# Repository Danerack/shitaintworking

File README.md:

4dawg Im about to tweak out rn

why is Hackatime and summer not workingggg
4rncrf htn unjth j

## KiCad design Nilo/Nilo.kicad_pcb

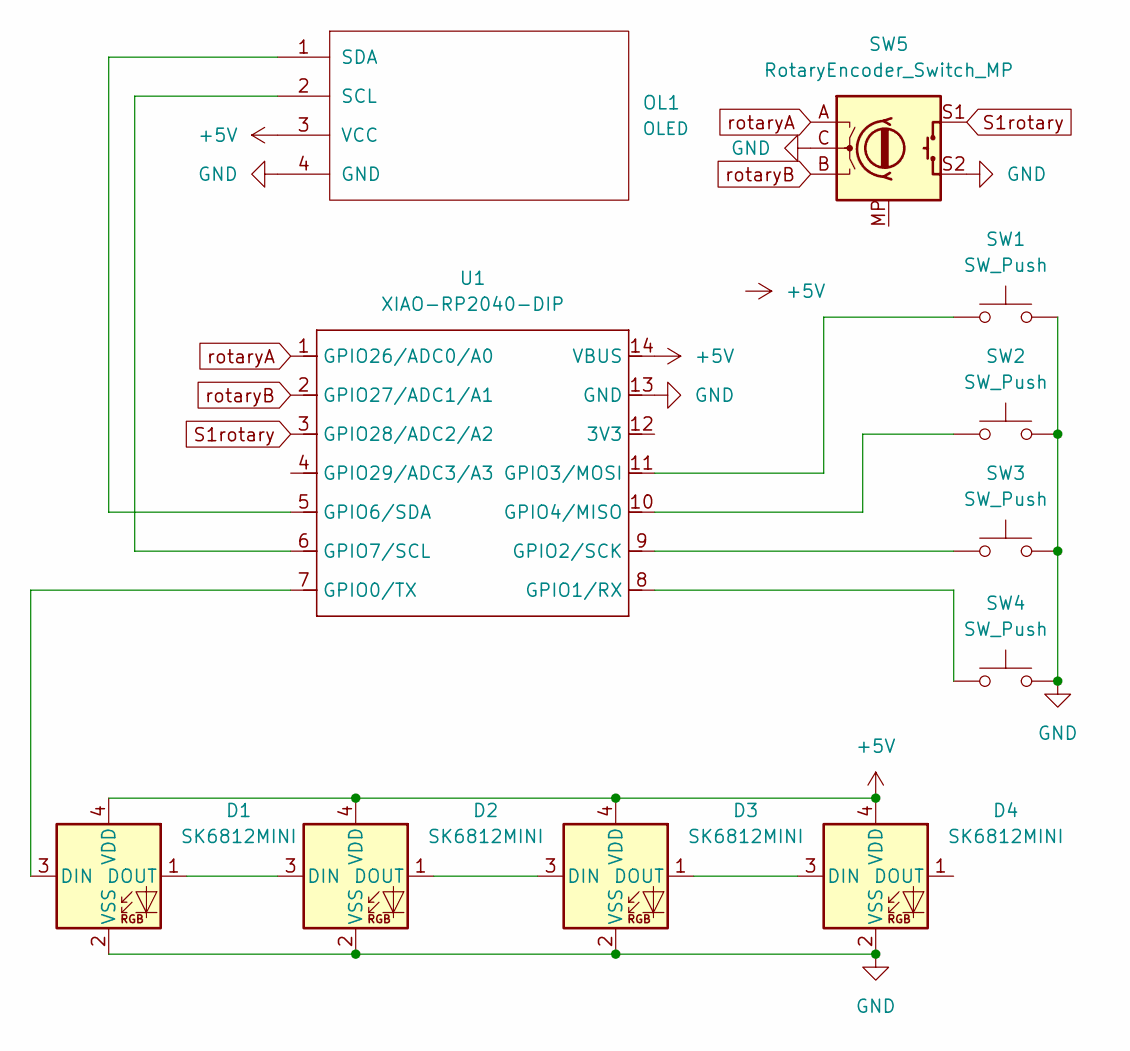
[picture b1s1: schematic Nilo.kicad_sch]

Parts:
D1, D2, D3, D4: SK6812MINI; LED_SK6812MINI_PLCC4_3.5x3.5mm_P1.75mm_3D
OL1: OLED
SW1, SW2, SW3, SW4: SW_Push; SW_Cherry_MX_1.00u_PCB_3D
SW5: RotaryEncoder_Switch_MP; RotaryEncoder_Alps_EC11E-Switch_Vertical_H20mm_3D
U1: XIAO-RP2040-DIP; XIAO-RP2040-DIP_3D

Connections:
+5V: D1.4 (VDD), D2.4 (VDD), D3.4 (VDD), D4.4 (VDD), OL1.3 (VCC), U1.14 (VBUS)
GND: D1.2 (VSS), D2.2 (VSS), D3.2 (VSS), D4.2 (VSS), OL1.4 (GND), SW1.2, SW2.2, SW3.2, SW4.2, SW5.C, SW5.S2, U1.13 (GND)
unnamed: D1.3 (DIN), U1.7 (GPIO0/TX)
unnamed: D1.1 (DOUT), D2.3 (DIN)
unnamed: D2.1 (DOUT), D3.3 (DIN)
unnamed: D3.1 (DOUT), D4.3 (DIN)
unnamed: OL1.2 (SCL), U1.6 (GPIO7/SCL)
unnamed: OL1.1 (SDA), U1.5 (GPIO6/SDA)
unnamed: SW4.1, U1.8 (GPIO1/RX)
unnamed: SW3.1, U1.9 (GPIO2/SCK)
unnamed: SW1.1, U1.11 (GPIO3/MOSI)
unnamed: SW2.1, U1.10 (GPIO4/MISO)
S1rotary: SW5.S1, U1.3 (GPIO28/ADC2/A2)
rotaryA: SW5.A, U1.1 (GPIO26/ADC0/A0)
rotaryB: SW5.B, U1.2 (GPIO27/ADC1/A1)

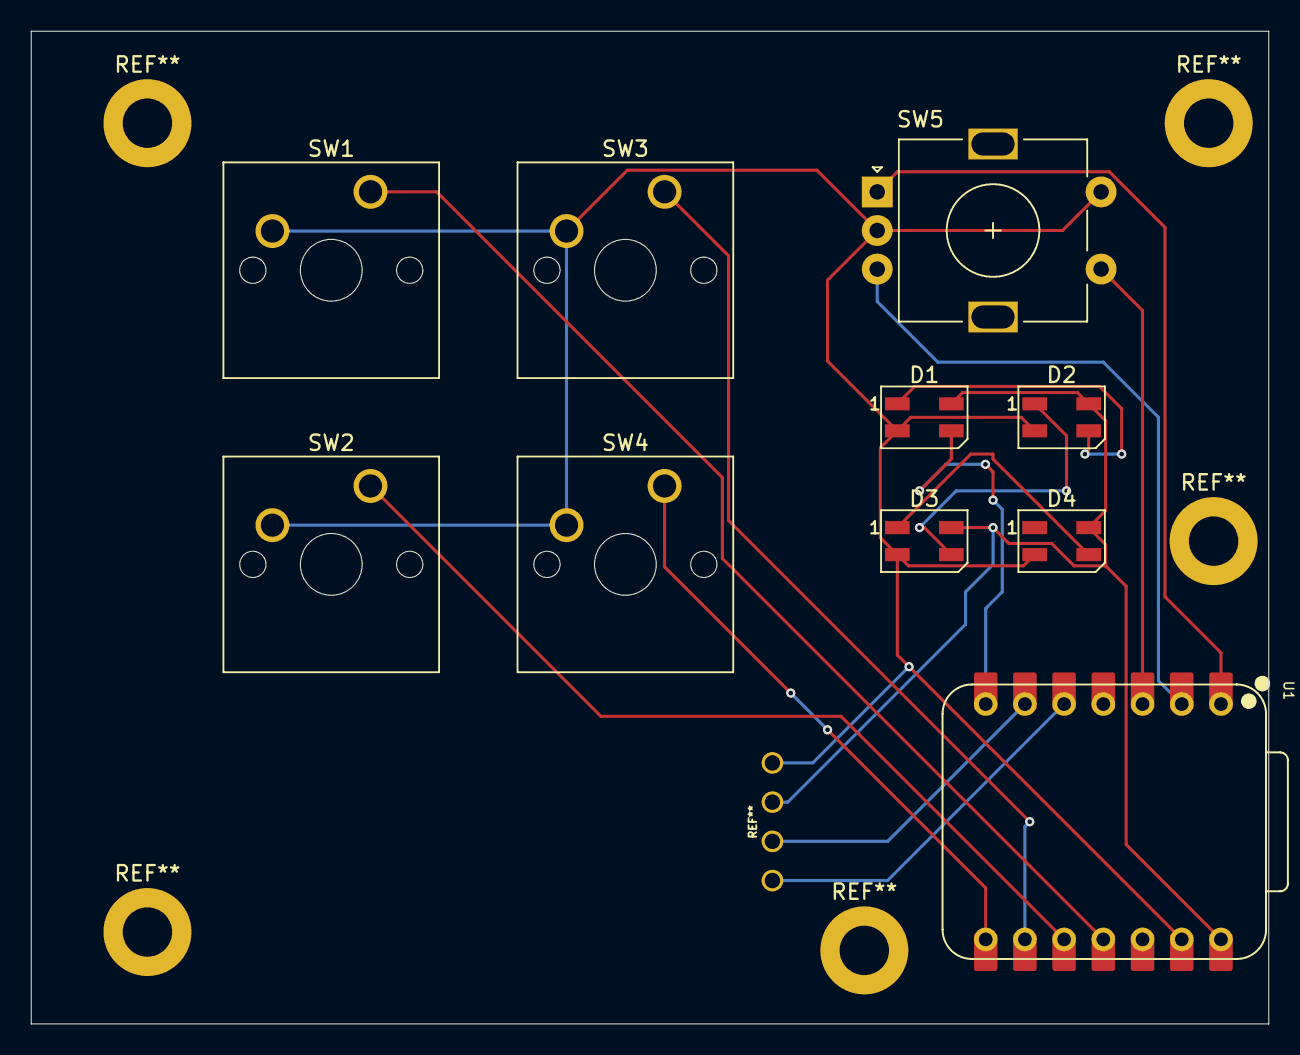
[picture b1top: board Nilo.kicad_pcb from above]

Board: 2 copper layers, 80.1 x 64.3 mm, 11 parts (0 on the bottom side), 15 nets.
